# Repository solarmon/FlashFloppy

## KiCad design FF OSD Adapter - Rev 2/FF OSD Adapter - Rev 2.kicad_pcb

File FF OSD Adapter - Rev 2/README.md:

# FF OSD Adapter - Rev 2

This adapter allows a FF OSD Blue Pill to be easily connected to a Gotek and a supported Amiga RGBtoHDMI adapter.

keirf's FF OSD: https://github.com/keirf/FF_OSD

Supported RGBtoHDMI boards: https://github.com/solarmon/RGBtoHDMI

## Rev 2

Improvements in Rev 2 include:

* Added support for 3 x button signals from RGBtoHDMI board, to allow for keyboard integration.
  - **Note:** This requires a custom build for custom hotkeys to be mapped to the button signals - see https://github.com/solarmon/FF_OSD 

Top:

Bottom:

Schematics PDF: https://github.com/solarmon/FlashFloppy/blob/main/FF%20OSD%20Adapter%20-%20Rev%202/FF%20OSD%20Adapter%20-%20Rev%202.pdf

## FF OSD Firmware ##

In order to support keyboard integration for the RGBtoHDMI menu buttons , FF OSD needs to be built with support for it. I have forked off the FF OSD files and have provided the example config required to build it with RGBtoHDMI button support - see:

https://github.com/solarmon/FF_OSD

The only change is to add the button code to `src/default_config.c`:

```c
#if 1
    /* An example for RGBtoHDMI momentary buttons */
    .user_pin_opendrain = U(2) | U(1) | U(0),	/* Set these pins as open drain */
    .user_pin_pushpull  = 0,					/* No buttons as pushpull */
	.user_pin_high		= U(2) | U(1) | U(0),	/* Initialise then as HIGH */

    .hotkey = {
        [F(1)]  = { .str = "RGBtoHDMI\0Button 1",	/* Test OSD text */
                    .pin_mod  = U(0), 
					.flags = HKF_momentary, },
        [F(2)]  = { .str = "RGBtoHDMI\0Button 2",	/* Test OSD text */
                    .pin_mod  = U(1), 
					.flags = HKF_momentary, },
		[F(3)]  = { .str = "RGBtoHDMI\0Button 3",	/* Test OSD text */
                    .pin_mod  = U(2), 
					.flags = HKF_momentary, },
    }
#endif
```
So you can take the original and latest source code from https://github.com/keirf/flashfloppy-osd and update `src/default_config.c` to include this three button mapping, and build the Blue Pill firmware yourself (see https://github.com/keirf/flashfloppy-osd/wiki/Building-From-Source)

## Installation and Connectivity

Here is an example summary installation connectivity with a supported RGBtoHDMI board and Gotek.

For dual output of FF OSD on Amiga RGB and RGBtoHDMI HDMI, use the FF OSD menu to set the option **Display Enable** to **A15** and to set **A15** to **Active Low**.

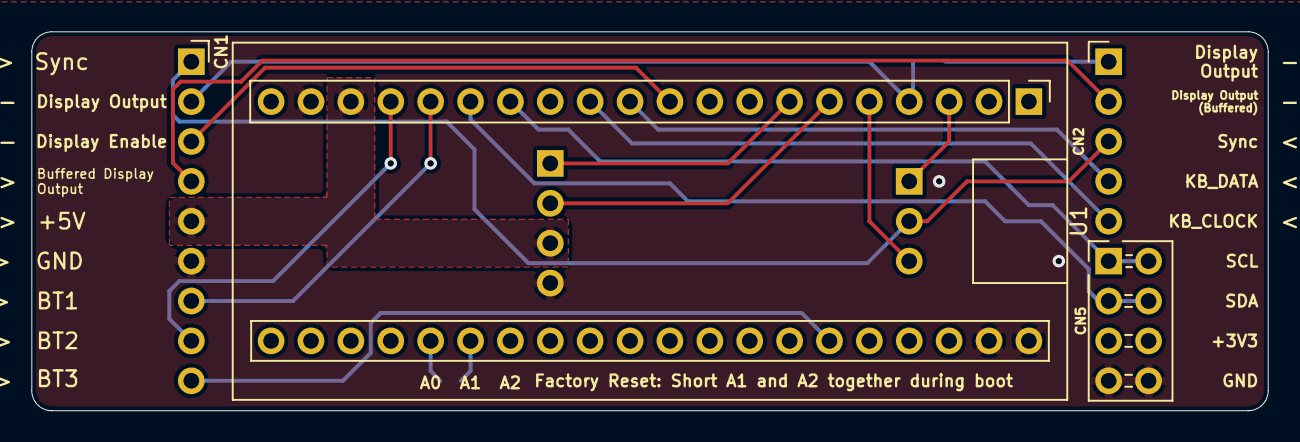
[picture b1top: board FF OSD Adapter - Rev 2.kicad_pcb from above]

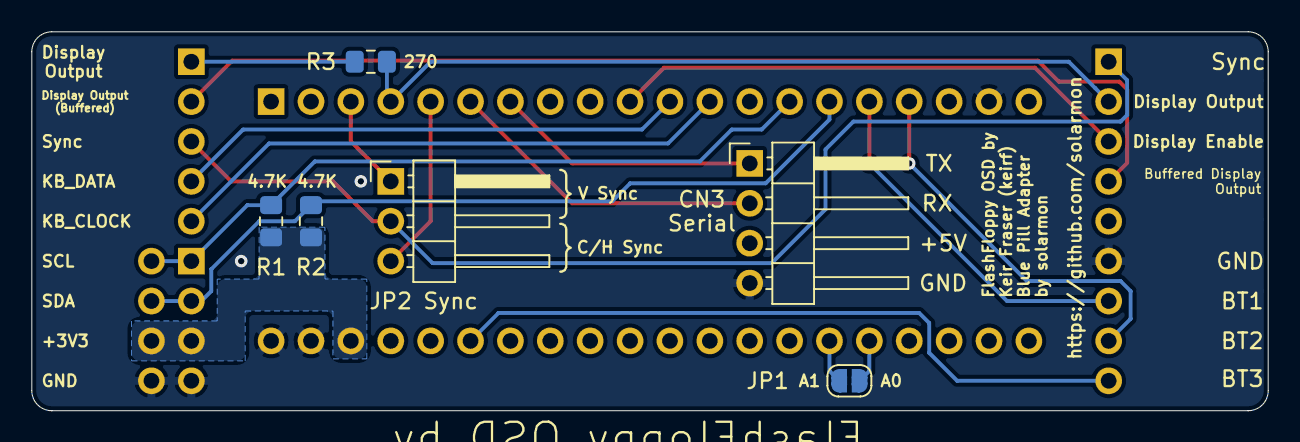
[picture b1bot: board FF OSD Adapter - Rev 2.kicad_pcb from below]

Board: 2 copper layers, 78.7 x 24.1 mm, 10 parts (6 on the bottom side), 21 nets.

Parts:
CN1: Conn_01x09; PinSocket_1x09_P2.54mm_Horizontal
CN2: Conn_01x05; PinHeader_1x05_P2.54mm_Horizontal
CN3: Conn_01x04; PinHeader_1x04_P2.54mm_Horizontal
CN5: Conn_02x04_Row_Letter_First; PinHeader_2x04_P2.54mm_Horizontal
JP1: Conn_01x02; SolderJumper-2_P1.3mm_Open_RoundedPad1.0x1.5mm
JP2: Conn_01x03; PinHeader_1x03_P2.54mm_Horizontal
R1, R2: 4.7K; R_0805_2012Metric_Pad1.15x1.40mm_HandSolder
R3: 270; R_0805_2012Metric_Pad1.15x1.40mm_HandSolder
U1: YAAJ_BluePill_Part_Like; YAAJ_BluePill_2

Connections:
+3V3: CN5.5, CN5.6, R1.2, R2.2, U1.38
+5V: CN1.5, CN3.3, U1.18
A0: JP1.1, U1.25
A1: JP1.2, U1.26
BT1: CN1.7, U1.16
BT2: CN1.8, U1.17
BT3: CN1.9, U1.35
C_H_SYNC: JP2.3, U1.5
DISPLAY_ENABLE: CN1.3, U1.10
DISPLAY_OUTPUT: CN1.2, R3.1, U1.4
DISPLAY_OUTPUT_BUFFERED: CN1.4, CN2.2
GND: CN1.6, CN3.4, CN5.7, CN5.8, U1.19, U1.39, U1.40
KB_CLOCK: CN2.5, U1.12
KB_DATA: CN2.4, U1.11
unnamed: CN2.1, R3.2
RX: CN3.1, U1.7
SCL: CN5.1, CN5.2, R1.1, U1.14
SDA: CN5.3, CN5.4, R2.1, U1.15
SYNC: CN1.1, CN2.3, JP2.2
TX: CN3.2, U1.6
V_SYNC: JP2.1, U1.3

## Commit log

2021-04-10 Added FF OSD Adapter
2021-04-10 Updated link to Blue Pill 3D model
2021-05-16 Added PNG and PDF files
2021-05-16 Added "FF OSD Adapter - Rev 2" project
2021-05-16 Added PND and PDF files
2021-05-19 Updated schematic and board to show the I2C display pins better
2021-05-19 Updated schematics
2021-07-24 Added integration diagrams
2021-07-24 Link to forked FF OSD files
